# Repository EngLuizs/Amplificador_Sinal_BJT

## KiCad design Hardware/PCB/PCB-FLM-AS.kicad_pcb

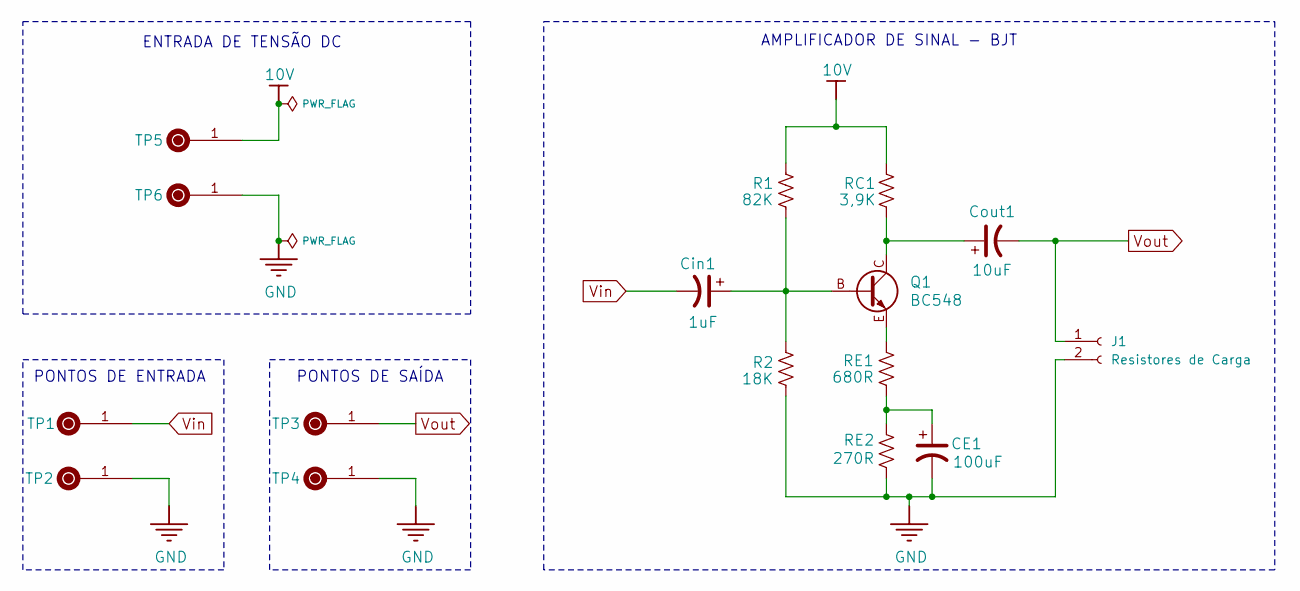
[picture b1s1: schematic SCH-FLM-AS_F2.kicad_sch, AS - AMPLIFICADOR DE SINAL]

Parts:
CE1: 100uF; CP_Radial_D8.0mm_P3.50mm
Cin1: 1uF; CP_Radial_D8.0mm_P3.50mm
Cout1: 10uF; CP_Radial_D8.0mm_P3.50mm
J1: Resistores de Carga; PinSocket_1x02_P2.54mm_Vertical
Q1: BC548; TRANSP(CBE)_BC548
R1: 82K; R_Axial_DIN0207_L6.3mm_D2.5mm_P7.62mm_Horizontal
R2: 18K; R_Axial_DIN0207_L6.3mm_D2.5mm_P7.62mm_Horizontal
RC1: 3,9K; R_Axial_DIN0207_L6.3mm_D2.5mm_P7.62mm_Horizontal
RE1: 680R; R_Axial_DIN0207_L6.3mm_D2.5mm_P7.62mm_Horizontal
RE2: 270R; R_Axial_DIN0207_L6.3mm_D2.5mm_P7.62mm_Horizontal
TP1: Vin; P_TESTE
TP2, TP4, TP5, TP6: GND; P_TESTE
TP3: Vout; P_TESTE

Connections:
10V: R1.2, RC1.2, TP5.1
GND: CE1.2, J1.2, R2.1, RE2.1, TP2.1, TP4.1, TP6.1; also elsewhere on the board
unnamed: CE1.1, RE1.1, RE2.2
unnamed: Cin1.1, Q1.B, R1.1, R2.2
unnamed: Cout1.1, Q1.C, RC1.1
unnamed: Q1.E, RE1.2
Vin: Cin1.2, TP1.1
Vout: Cout1.2, J1.1, TP3.1; also elsewhere on the board

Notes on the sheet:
PONTOS DE SAÍDA
PONTOS DE ENTRADA
AMPLIFICADOR DE SINAL - BJT
ENTRADA DE TENSÃO DC

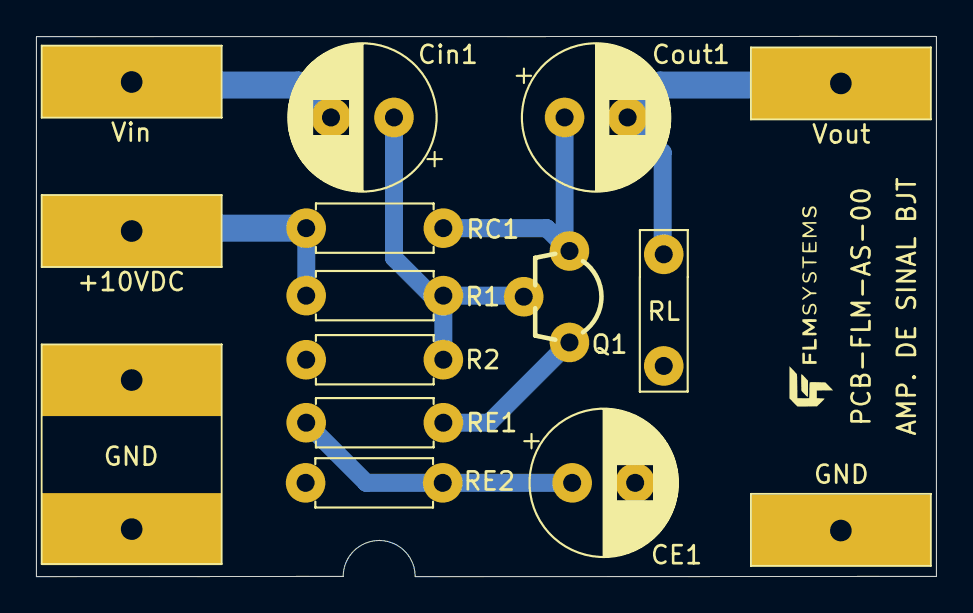
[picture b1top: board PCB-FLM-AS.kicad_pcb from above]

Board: 2 copper layers, 50.0 x 30.0 mm, 16 parts (0 on the bottom side), 8 nets.

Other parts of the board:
RL: Resistores de Carga; PinSocket_1x02_P2.54mm_Vertical

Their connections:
GND: RL.2; also elsewhere on the board
Vout: RL.1; also elsewhere on the board
